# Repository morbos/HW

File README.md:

This is a collection of my Kicad board projects

all_in_one: a scion from Teapot Lab's bwlr1e (https://github.com/teapotlaboratories/bwlr1e)

door3: an LIS3MDL magnetometer breakout.

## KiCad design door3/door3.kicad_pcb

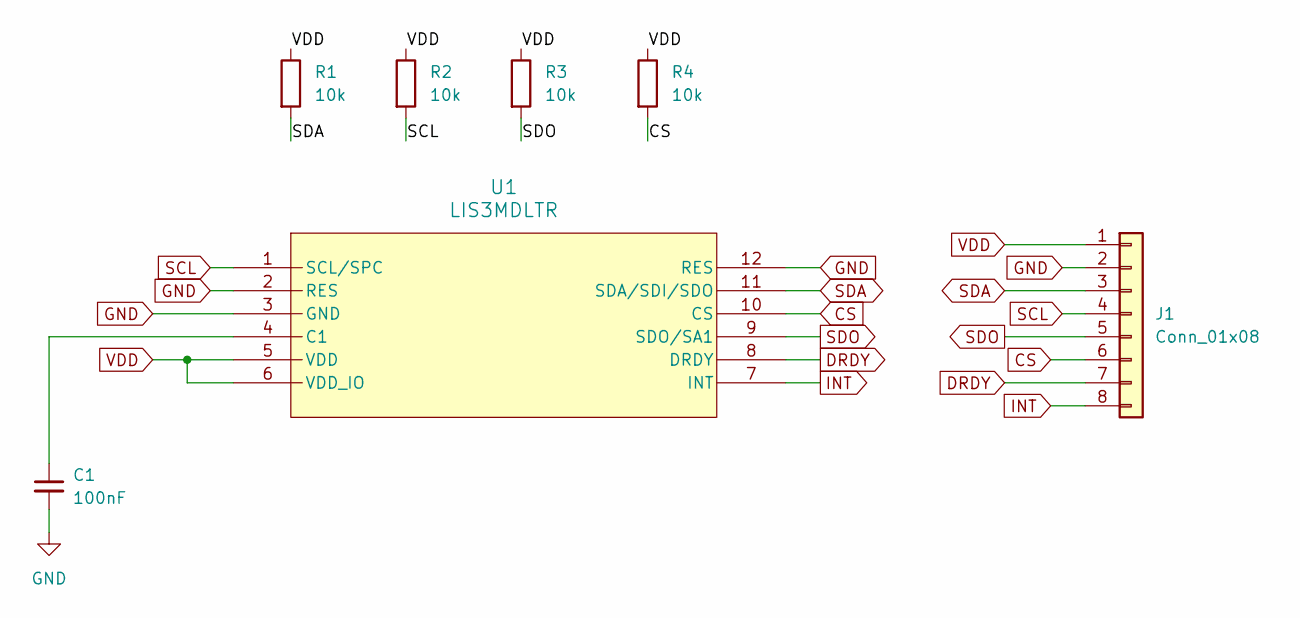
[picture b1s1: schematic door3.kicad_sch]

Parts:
C1: 100nF; C_0603_1608Metric
J1: Conn_01x08; PinHeader_1x08_P2.54mm_Vertical
R1, R2, R3, R4: 10k; R_0603_1608Metric
U1: LIS3MDLTR; LGA-12_2X2X1_STM

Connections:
CS: J1.6, R4.2, U1.10 (CS)
DRDY: J1.7, U1.8 (DRDY)
GND: C1.2, J1.2, U1.2 (RES), U1.3 (GND), U1.12 (RES)
INT: J1.8, U1.7 (INT)
unnamed: C1.1, U1.4 (C1)
SCL: J1.4, R2.2, U1.1 (SCL/SPC)
SDA: J1.3, R1.2, U1.11 (SDA/SDI/SDO)
SDO: J1.5, R3.2, U1.9 (SDO/SA1)
VDD: J1.1, R1.1, R2.1, R3.1, R4.1, U1.5 (VDD), U1.6 (VDD_IO)

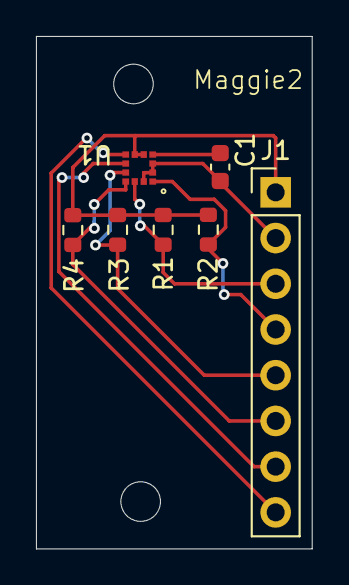
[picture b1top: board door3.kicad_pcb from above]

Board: 2 copper layers, 15.3 x 28.5 mm, 7 parts (0 on the bottom side), 9 nets.

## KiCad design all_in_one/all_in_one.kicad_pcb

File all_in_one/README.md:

This is a rollup of 3 bits of HW. It is based on the excellent work by Teapot labs's project bwlr1e

https://github.com/teapotlaboratories/bwlr1e

The Teapot Labs design is very good but I wanted a few changes:

1) External battery. Two methods to connect.
2) External solar panel. Two methods to connect.
3) LIS3MDL magnetometer vs BME688 for my sensing needs.
4) Use external antenna vs board antenna
5) CDS light sensor input
6) Dupont headers for external parts vs quic connects.
7) Sized to fit on my hot plate.

Software for this is in dirs denoted by <dir>_aio (all in one)

ex:
https://github.com/morbos/ada/tree/main/STM32/WL/WL5J/door2_aio

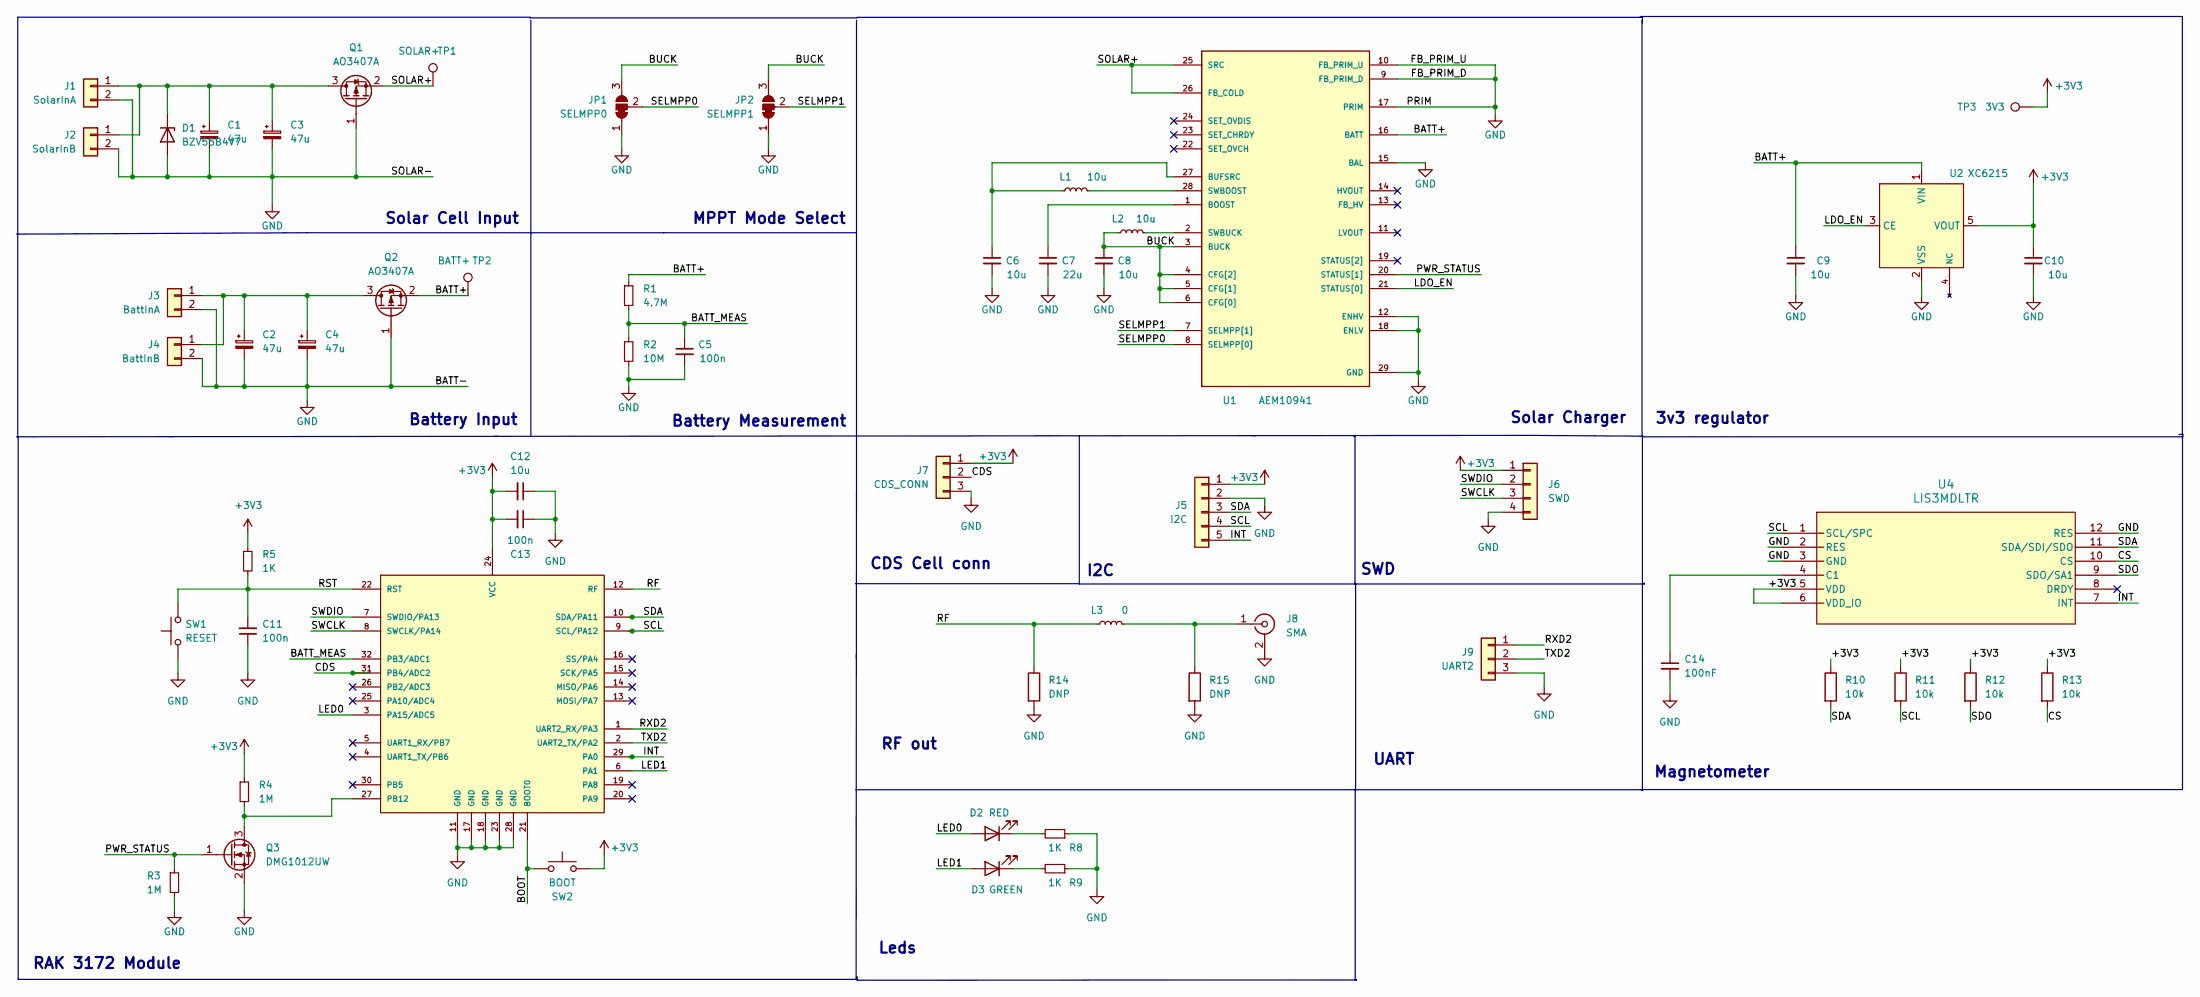
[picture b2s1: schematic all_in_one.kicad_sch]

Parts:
C1, C2, C3, C4: 47u; CP_EIA-3528-15_AVX-H_Pad1.50x2.35mm_HandSolder; Part Number TPSB476K010R0350
C5, C11, C13: 100n; C_0603_1608Metric_Pad1.08x0.95mm_HandSolder; Part Description Ceramic Capacitor 100nF 10% 10V X7R
C6: 10u; C_0603_1608Metric; Part Description Ceramic Capacitor 10uF 10% 10V X5R
C7: 22u; C_0603_1608Metric_Pad1.08x0.95mm_HandSolder; Part Description Ceramic Capacitor 22uF 20% 10V X5R
C8, C9, C10, C12: 10u; C_0603_1608Metric_Pad1.08x0.95mm_HandSolder; Part Description Ceramic Capacitor 10uF 10% 10V X5R
C14: 100nF; C_0603_1608Metric
D1: BZV55B4V7; D_MiniMELF
D2: RED; LED_0603_1608Metric_Pad1.05x0.95mm_HandSolder; Part Description Red 2V 20mA
D3: GREEN; LED_0603_1608Metric_Pad1.05x0.95mm_HandSolder; Part Description Green 2V 20mA
J1: SolarInA; PinHeader_1x02_P2.54mm_Vertical
J2: SolarInB; TerminalBlock_Phoenix_MPT-0,5-2-2.54_1x02_P2.54mm_Horizontal
J3: BattInA; PinHeader_1x02_P2.54mm_Vertical
J4: BattInB; TerminalBlock_Phoenix_MPT-0,5-2-2.54_1x02_P2.54mm_Horizontal
J5: I2C; PinHeader_1x05_P2.54mm_Vertical
J6: SWD; PinHeader_1x04_P2.54mm_Vertical; Part Number SM04B-SRSS-TB
J7: CDS_CONN; PinHeader_1x03_P2.54mm_Vertical
J8: SMA; SMA_Amphenol_132134-14_Vertical
J9: UART2; PinHeader_1x03_P2.54mm_Vertical
JP1: SELMPP0; SolderJumper-3_P1.3mm_Bridged12_RoundedPad1.0x1.5mm_NumberL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
JP2: SELMPP1; SolderJumper-3_P1.3mm_Bridged12_RoundedPad1.0x1.5mm_NumberL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
L1: 10u; IND_LPS4012-103MRB; Part Description Power Inductor 10uH 20% 1.1A
L2: 10u; L_0603_1608Metric_Pad1.05x0.95mm_HandSolder; Part Description Power Inductor 10uH 20% 90mA
L3: 0; L_0603_1608Metric_Pad1.05x0.95mm_HandSolder; Part Description Power Inductor 10uH 20% 90mA
Q1, Q2: AO3407A; SOT-23; Part Number AO3407A
Q3: DMG1012UW; SOT-323_SC-70; Part Number DMG1012UW
R1: 4.7M; R_0603_1608Metric_Pad0.98x0.95mm_HandSolder; Part Description Resistor 4.7M 1% 100mW
R2: 10M; R_0603_1608Metric_Pad0.98x0.95mm_HandSolder; Part Description Resistor 10M 1% 100mW
R3, R4: 1M; R_0603_1608Metric_Pad0.98x0.95mm_HandSolder; Part Description Resistor 1M 5% 100mW
R5, R8, R9: 1K; R_0603_1608Metric_Pad0.98x0.95mm_HandSolder; Part Description Resistor 1K 5% 100mW
R10, R11, R12, R13: 10k; R_0603_1608Metric
R14, R15: DNP; R_0603_1608Metric
SW1: RESET; SW_SPST_TL3342; Part Number TL3342F160QG
SW2: BOOT; SW_SPST_TL3342; Part Number TL3342F160QG
TP1: SOLAR+; TestPoint_Pad_D1.0mm
TP2: BATT+; TestPoint_Pad_D1.0mm
TP3: 3V3; TestPoint_Pad_D1.0mm
U1: AEM10941; QFN-28-1EP_5x5mm_P0.5mm_EP3.35x3.35mm; Part Number AEM10941-QFN
U2: XC6215; SOT-23-5; Part Number XC6215B332MR-G
U3: RAK3172-T; RAK3172; Part Number 309054
U4: LIS3MDLTR; LGA-12_2X2X1_STM

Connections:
+3V3: C10.1, C12.2, C13.2, J5.1, J6.1, J7.1, R4.1, R5.1, R10.1, R11.1, R12.1, R13.1, SW2.2, TP3.1, U2.5 (VOUT), U3.24 (VCC), U4.5 (VDD), U4.6 (VDD_IO)
/BATT+: C9.1, Q2.2 (S), R1.1, TP2.1, U1.16 (BATT), U2.1 (VIN)
/BATT_MEAS: C5.1, R1.2, R2.1, U3.32 (PB3/ADC1)
/BOOT: SW2.1, U3.21 (BOOT0)
/BUCK: C8.1, JP1.3 (B), JP2.3 (B), L2.1, U1.3 (BUCK), U1.4 (CFG[2]), U1.5 (CFG[1]), U1.6 (CFG[0])
/CDS: J7.2, U3.31 (PB4/ADC2)
/CS: R13.2, U4.10 (CS)
/INT: J5.5, U3.29 (PA0), U4.7 (INT)
/LDO_EN: U1.21 (STATUS[0]), U2.3 (CE)
/LED0: D2.2 (A), U3.3 (PA15/ADC5)
/LED1: D3.2 (A), U3.6 (PA1)
/PWR_STATUS: Q3.1 (G), R3.1, U1.20 (STATUS[1])
/RF: L3.1, R14.1, U3.12 (RF)
/RST: C11.2, R5.2, SW1.2, U3.22 (RST)
/RXD2: J9.1, U3.1 (UART2_RX/PA3)
/SCL: J5.4, R11.2, U3.9 (SCL/PA12), U4.1 (SCL/SPC)
/SDA: J5.3, R10.2, U3.10 (SDA/PA11), U4.11 (SDA/SDI/SDO)
/SDO: R12.2, U4.9 (SDO/SA1)
/SELMPP0: JP1.2 (C), U1.8 (SELMPP[0])
/SELMPP1: JP2.2 (C), U1.7 (SELMPP[1])
/SOLAR+: Q1.2 (S), TP1.1, U1.25 (SRC), U1.26 (FB_COLD)
/SWCLK: J6.3, U3.8 (SWCLK/PA14)
/SWDIO: J6.2, U3.7 (SWDIO/PA13)
/TXD2: J9.2, U3.2 (UART2_TX/PA2)
GND: C1.2, C2.2, C3.2, C4.2, C5.2, C6.2, C7.2, C8.2, C9.2, C10.2, C11.1, C12.1, C13.1, C14.2, D1.2 (A), J1.2, J2.2, J3.2, J4.2, J5.2, J6.4, J7.3, J8.2 (Ext), J9.3, JP1.1 (A), JP2.1 (A), Q1.1 (G), Q2.1 (G), Q3.2 (S), R2.2, R3.2, R8.1, R9.1, R14.2, R15.2, SW1.1, U1.9 (FB_PRIM_D), U1.10 (FB_PRIM_U), U1.12 (ENHV), U1.15 (BAL), U1.17 (PRIM), U1.18 (ENLV), U1.29 (GND), U2.2 (VSS), U3.11 (GND), U3.17 (GND), U3.18 (GND), U3.23 (GND), U3.28 (GND), U4.2 (RES), U4.3 (GND), U4.12 (RES)
unnamed: C1.1, C3.1, D1.1 (K), J1.1, J2.1, Q1.3 (D)
unnamed: D2.1 (K), R8.2
unnamed: D3.1 (K), R9.2
unnamed: C2.1, C4.1, J3.1, J4.1, Q2.3 (D)
unnamed: J8.1 (In), L3.2, R15.1
unnamed: Q3.3 (D), R4.2, U3.27 (PB12)
unnamed: C7.1, U1.1 (BOOST)
unnamed: C6.1, L1.1, U1.27 (BUFSRC)
unnamed: L1.2, U1.28 (SWBOOST)
unnamed: L2.2, U1.2 (SWBUCK)
unnamed: C14.1, U4.4 (C1)

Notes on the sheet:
3v3 regulator
Battery Measurement
Magnetometer
SWD
Leds
UART
Solar Cell Input
CDS Cell conn
Battery Input
I2C
Solar Charger
MPPT Mode Select
RF out
RAK 3172 Module

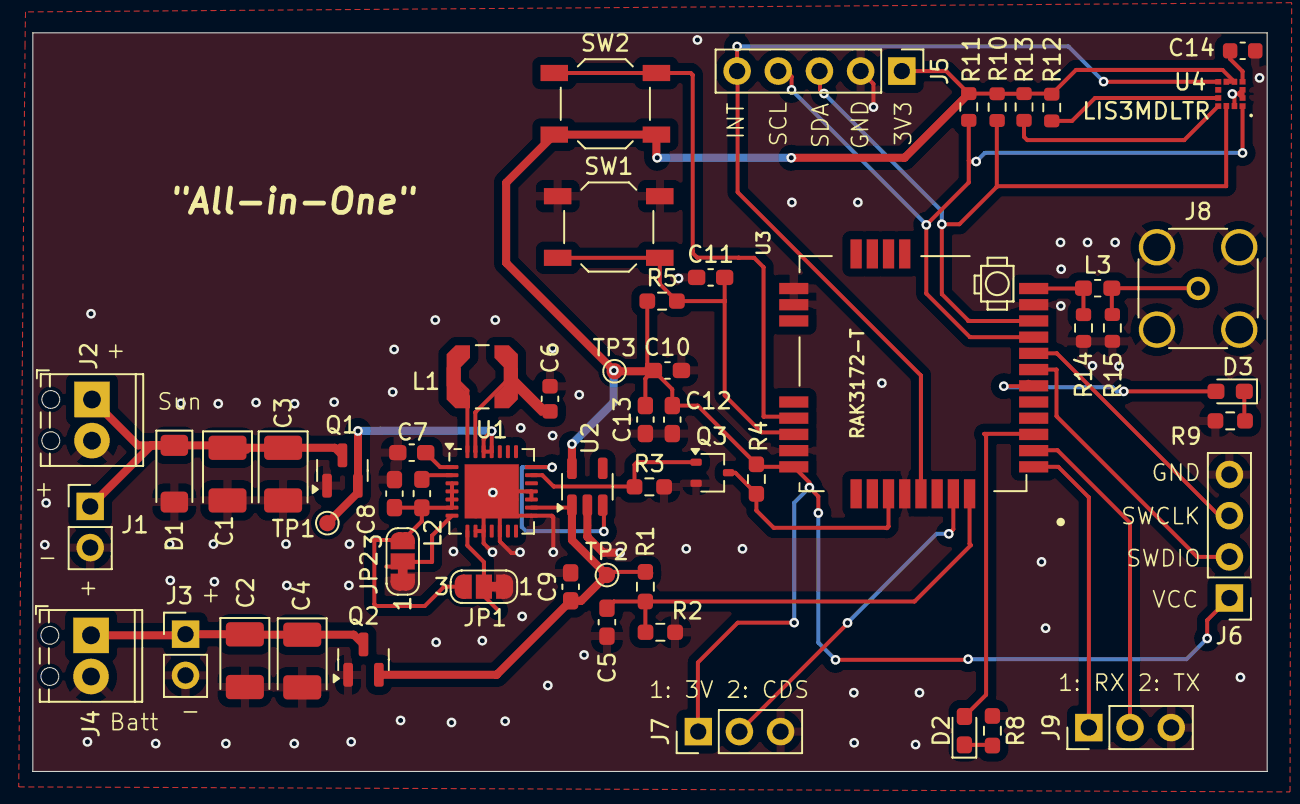
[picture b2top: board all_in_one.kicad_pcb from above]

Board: 2 copper layers, 76.2 x 45.6 mm, 56 parts (0 on the bottom side), 36 nets.

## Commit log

2025-04-15 Kicad boards
2025-04-15 Add the Kicad boards
2025-04-15 Add some pics
2025-04-15 - Update readme
